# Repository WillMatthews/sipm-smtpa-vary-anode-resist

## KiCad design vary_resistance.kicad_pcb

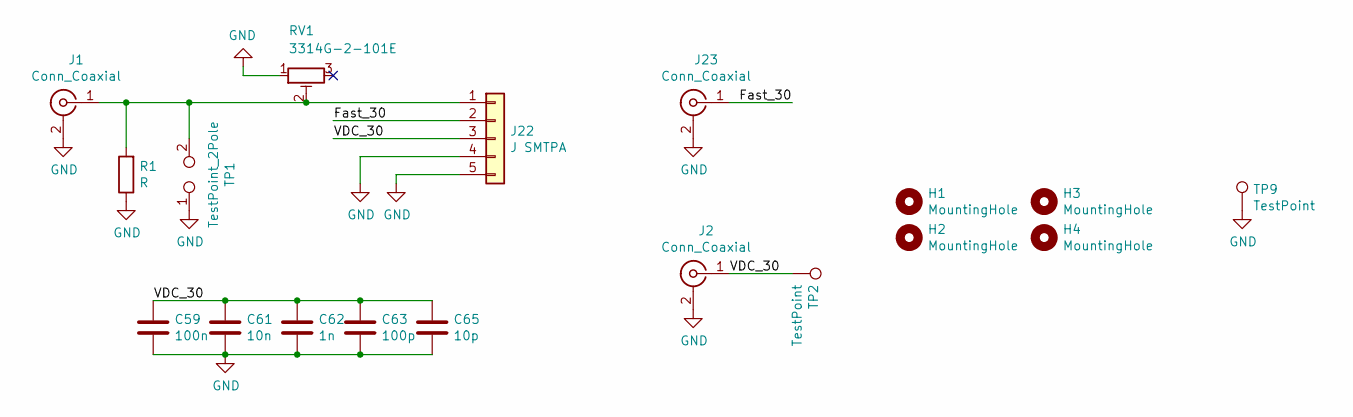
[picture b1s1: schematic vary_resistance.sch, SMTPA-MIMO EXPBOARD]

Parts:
C59: 100n; C_0603_1608Metric_Pad1.05x0.95mm_HandSolder
C61: 10n; C_0603_1608Metric_Pad1.05x0.95mm_HandSolder
C62: 1n; C_0603_1608Metric_Pad1.05x0.95mm_HandSolder
C63: 100p; C_0402_1005Metric
C65: 10p; C_0402_1005Metric
H1, H2, H3, H4: MountingHole; MountingHole_4.3mm_M4_Pad_Via
J1, J2, J23: Conn_Coaxial; SMA_Amphenol_132289_EdgeMount
J22: J SMTPA; SMTPA J30035
R1: R; R_0805_2012Metric_Pad1.15x1.40mm_HandSolder
RV1: 3314G-2-101E; Potentiometer_Bourns_3314G_Vertical; Part 987-1161-ND
TP1: TestPoint_2Pole; PinHeader_1x02_P2.54mm_Vertical
TP2, TP9: TestPoint; TestPoint_Pad_4.0x4.0mm

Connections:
/Fast_30: J22.2, J23.1 (In)
/VDC_30: C59.1, C61.1, C62.1, C63.1, C65.1, J2.1 (In), J22.3, TP2.1
GND: C59.2, C61.2, C62.2, C63.2, C65.2, J1.2 (Ext), J2.2 (Ext), J22.4, J22.5, J23.2 (Ext), R1.1, RV1.1, TP1.1, TP9.1
unnamed: J1.1 (In), J22.1, R1.2, RV1.2, TP1.2

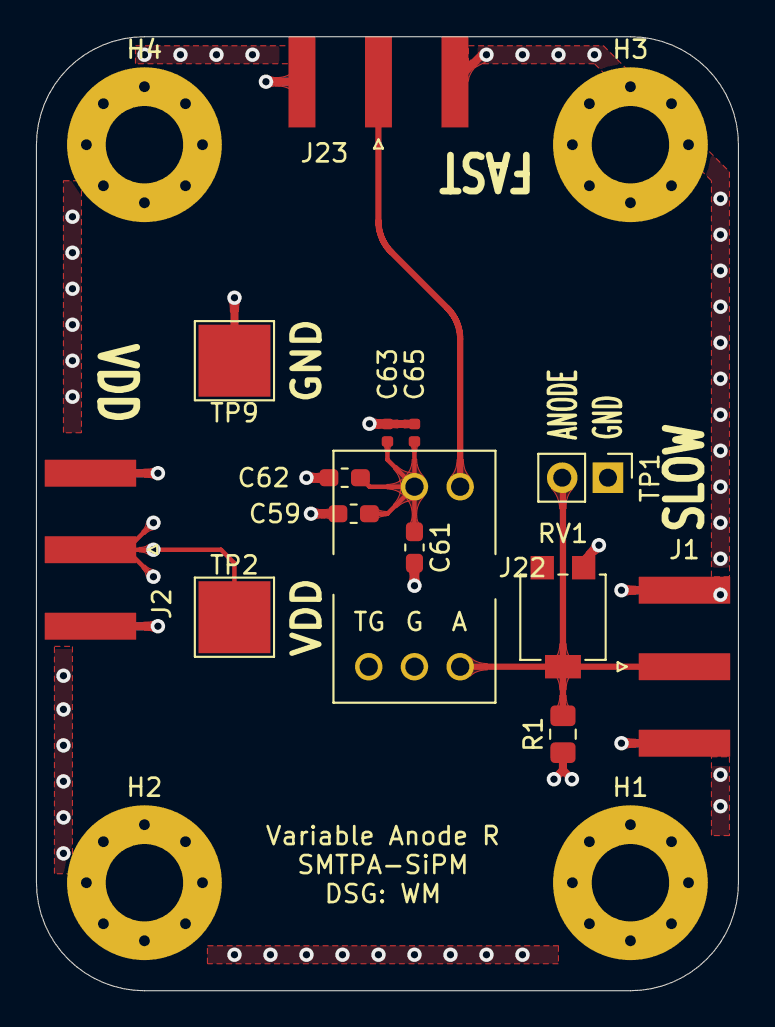
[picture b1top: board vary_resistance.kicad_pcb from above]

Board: 4 copper layers, 39.0 x 53.0 mm, 18 parts (0 on the bottom side), 4 nets.

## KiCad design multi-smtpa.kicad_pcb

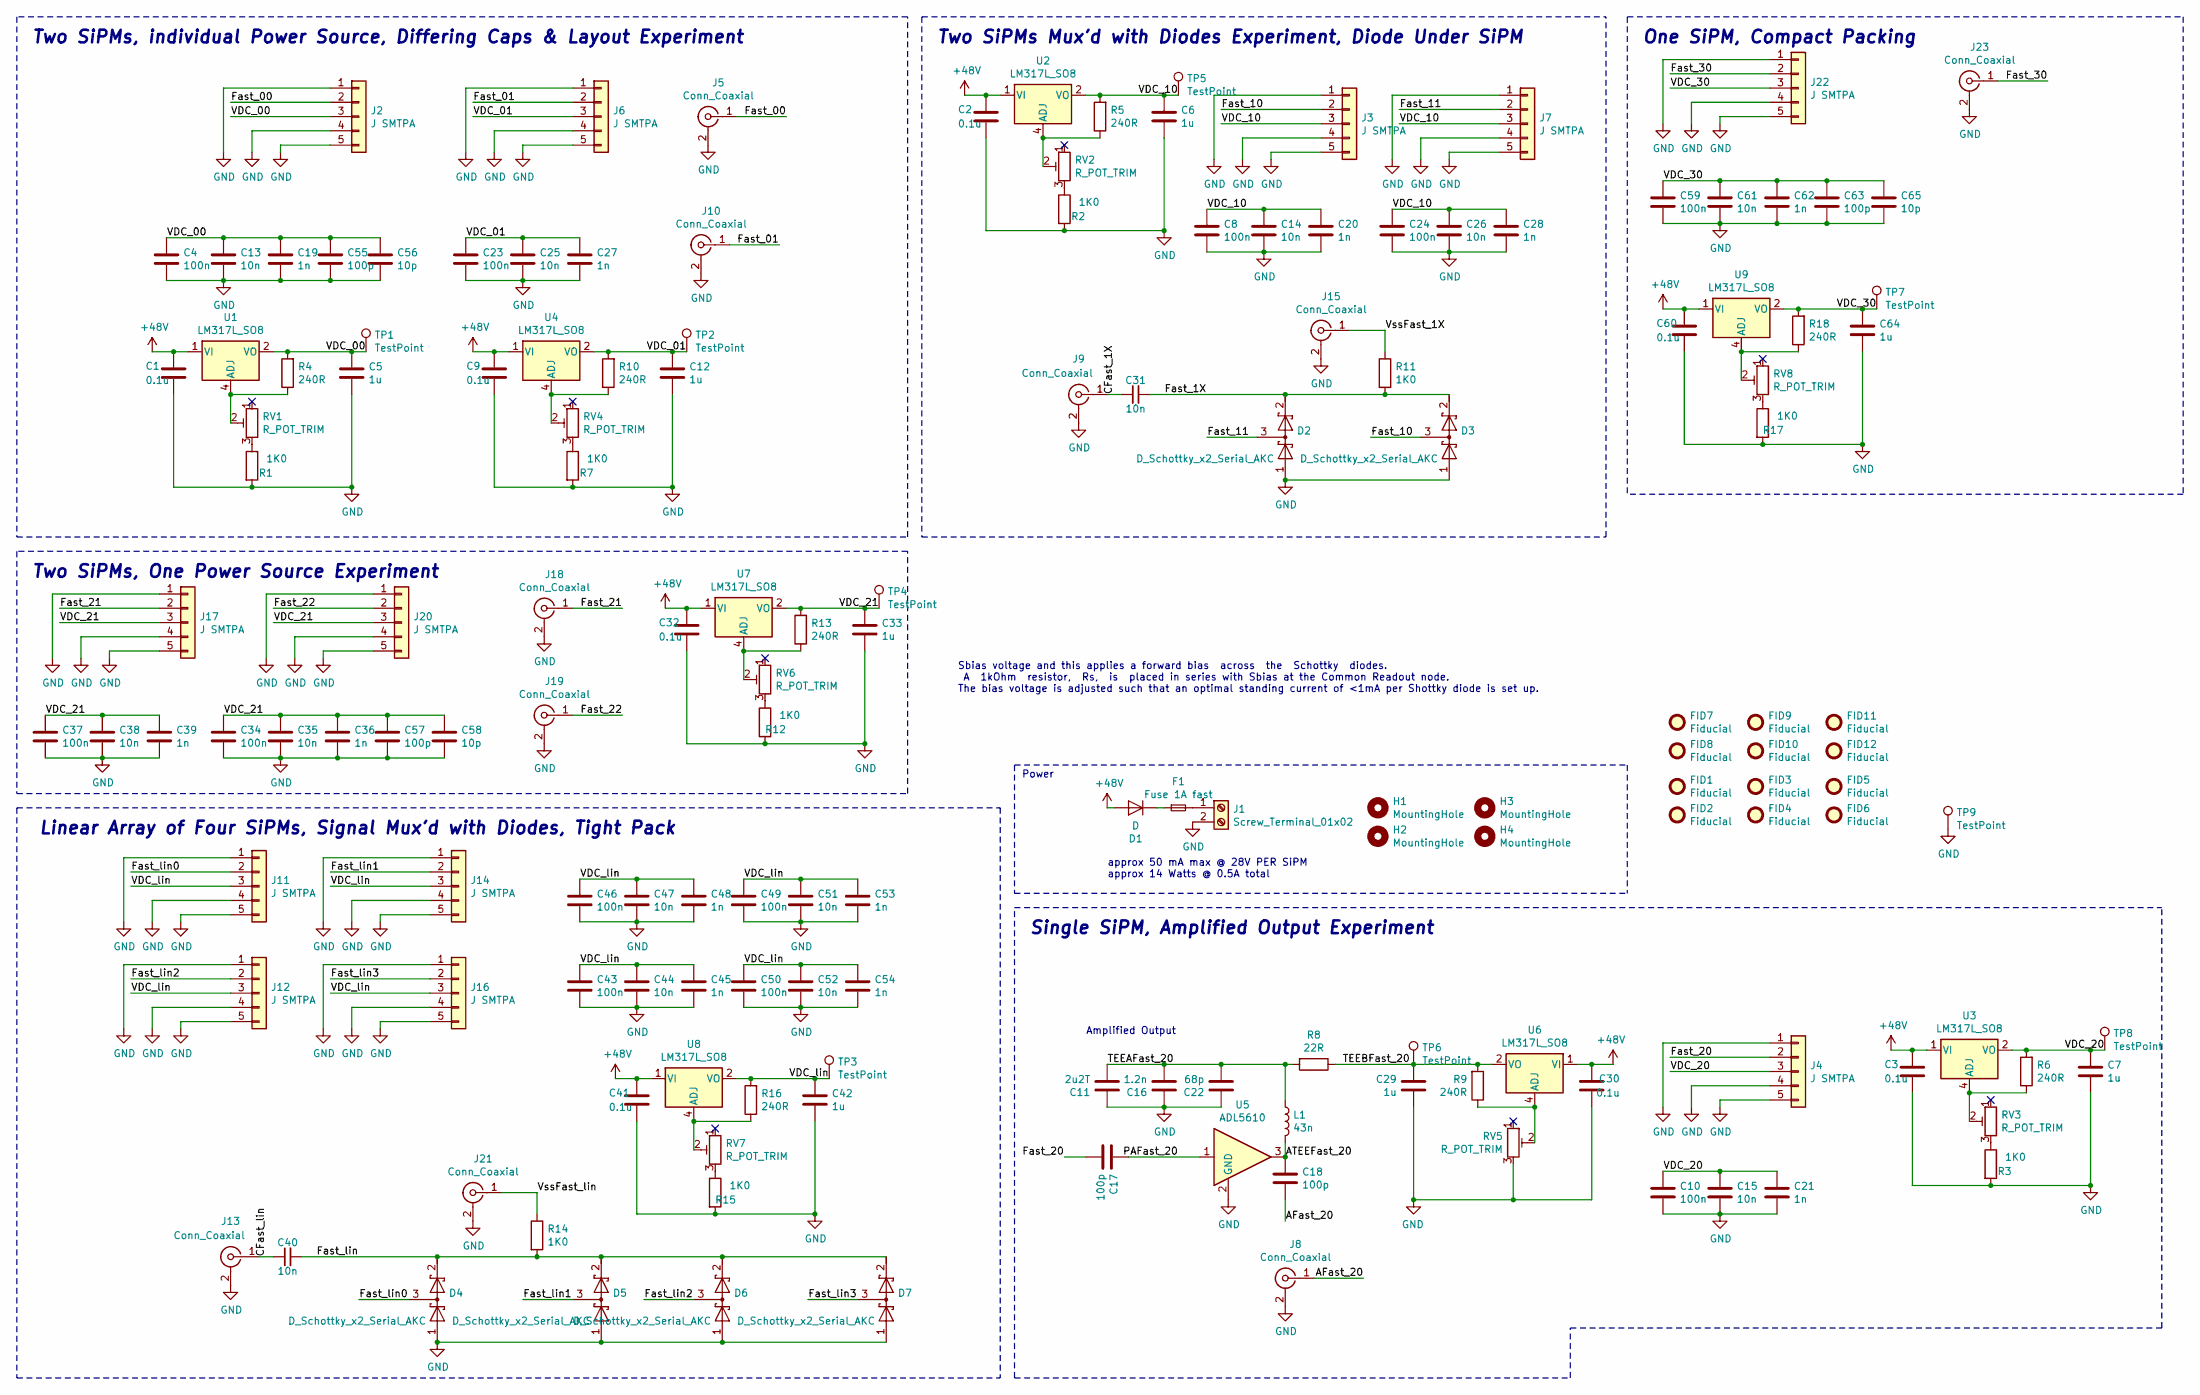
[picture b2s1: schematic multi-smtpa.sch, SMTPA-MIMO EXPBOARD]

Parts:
C1, C2, C3, C9, C30, C32, C41, C60: 0.1u; C_0805_2012Metric_Pad1.15x1.40mm_HandSolder
C4, C8, C10, C23, C24, C34, C37, C43, C46, C49, C50, C59: 100n; C_0603_1608Metric_Pad1.05x0.95mm_HandSolder
C5, C6, C7, C12, C29, C33, C42, C64: 1u; C_0805_2012Metric_Pad1.15x1.40mm_HandSolder
C11: 2u2T; C_0805_2012Metric_Pad1.15x1.40mm_HandSolder
C13, C14, C15, C25, C26, C31, C35, C38, C40, C44, C47, C51, C52, C61: 10n; C_0603_1608Metric_Pad1.05x0.95mm_HandSolder
C16: 1.2n; C_0603_1608Metric_Pad1.05x0.95mm_HandSolder
C17, C18: 100p; C_0603_1608Metric_Pad1.05x0.95mm_HandSolder
C19, C20, C21, C27, C28, C36, C39, C45, C48, C53, C54, C62: 1n; C_0603_1608Metric_Pad1.05x0.95mm_HandSolder
C22: 68p; C_0603_1608Metric_Pad1.05x0.95mm_HandSolder
C55, C57, C63: 100p; C_0402_1005Metric
C56, C58, C65: 10p; C_0402_1005Metric
D1: D; D_A-405_P10.16mm_Horizontal
D2, D3, D4, D5, D6, D7: D_Schottky_x2_Serial_AKC; SOT-23; Part SMS7621-005LF SOT23
F1: Fuse 1A fast; R_Axial_DIN0207_L6.3mm_D2.5mm_P10.16mm_Horizontal
FID1, FID2, FID3, FID4, FID5, FID6, FID7, FID8, FID9, FID10, FID11, FID12: Fiducial; Fiducial_1mm_Mask3mm
H1, H2, H3, H4: MountingHole; MountingHole_4.3mm_M4_Pad_Via
J1: Screw_Terminal_01x02; TerminalBlock_TE_282834-2_1x02_P2.54mm_Horizontal
J2, J3, J4, J6, J7, J11, J12, J14, J16, J17, J20, J22: J SMTPA; SMTPA J30035
J5, J8, J9, J10, J13, J15, J18, J19, J21, J23: Conn_Coaxial; SMA_Amphenol_132289_EdgeMount
L1: 43n; L_0402_1005Metric; part LQW15AN43NG00D
R1, R2, R3, R7, R12, R15, R17: 1K0; R_0805_2012Metric_Pad1.15x1.40mm_HandSolder
R4, R5, R6, R9, R10, R13, R16, R18: 240R; R_0805_2012Metric_Pad1.15x1.40mm_HandSolder
R8: 22R; R_0603_1608Metric_Pad1.05x0.95mm_HandSolder
R11, R14: 1K0; R_0603_1608Metric_Pad1.05x0.95mm_HandSolder
RV1, RV2, RV3, RV4, RV5, RV6, RV7: R_POT_TRIM; Potentiometer_Bourns_3006Y_Horizontal; Part 987-1161-ND
RV8: R_POT_TRIM; Potentiometer_Bourns_3314G_Vertical; Part 987-1161-ND
TP1, TP2, TP3, TP4, TP5, TP6, TP7, TP8: TestPoint; TestPoint_Pad_D2.0mm
TP9: TestPoint; TestPoint_Pad_4.0x4.0mm
U1, U2, U3, U4, U6, U7, U8, U9: LM317L_SO8; SOIC-8_3.9x4.9mm_P1.27mm; Part LM317LDR2GOSDKR-ND
U5: ADL5610; SOT-89-3

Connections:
+48V: C1.1, C2.1, C3.1, C9.1, C30.1, C32.1, C41.1, C60.1, D1.2 (A), U1.1 (VI), U2.1 (VI), U3.1 (VI), U4.1 (VI), U6.1 (VI), U7.1 (VI), U8.1 (VI), U9.1 (VI)
/AFast_20: C18.2, J8.1 (In)
/ATEEFast_20: C18.1, L1.2, U5.3
/CFast_1X: C31.1, J9.1 (In)
/CFast_lin: C40.1, J13.1 (In)
/Fast_00: J2.2, J5.1 (In)
/Fast_01: J6.2, J10.1 (In)
/Fast_1X: C31.2, D2.2 (K), D3.2 (K), R11.2
/Fast_10: D3.3 (common), J3.2
/Fast_11: D2.3 (common), J7.2
/Fast_20: C17.2, J4.2
/Fast_21: J17.2, J18.1 (In)
/Fast_22: J19.1 (In), J20.2
/Fast_30: J22.2, J23.1 (In)
/Fast_lin: C40.2, D4.2 (K), D5.2 (K), D6.2 (K), D7.2 (K), R14.2
/Fast_lin0: D4.3 (common), J11.2
/Fast_lin1: D5.3 (common), J14.2
/Fast_lin2: D6.3 (common), J12.2
/Fast_lin3: D7.3 (common), J16.2
/PAFast_20: C17.1, U5.1
/TEEAFast_20: C11.2, C16.2, C22.2, L1.1, R8.2
/TEEBFast_20: C29.1, R8.1, R9.2, TP6.1, U6.2 (VO), U6.3 (VO), U6.6 (VO), U6.7 (VO)
/VDC_00: C4.1, C5.1, C13.1, C19.1, C55.1, C56.1, J2.3, R4.2, TP1.1, U1.2 (VO), U1.3 (VO), U1.6 (VO), U1.7 (VO)
/VDC_01: C12.1, C23.1, C25.1, C27.1, J6.3, R10.2, TP2.1, U4.2 (VO), U4.3 (VO), U4.6 (VO), U4.7 (VO)
/VDC_10: C6.1, C8.1, C14.1, C20.1, C24.1, C26.1, C28.1, J3.3, J7.3, R5.2, TP5.1, U2.2 (VO), U2.3 (VO), U2.6 (VO), U2.7 (VO)
/VDC_20: C7.1, C10.1, C15.1, C21.1, J4.3, R6.2, TP8.1, U3.2 (VO), U3.3 (VO), U3.6 (VO), U3.7 (VO)
/VDC_21: C33.1, C34.1, C35.1, C36.1, C37.1, C38.1, C39.1, C57.1, C58.1, J17.3, J20.3, R13.2, TP4.1, U7.2 (VO), U7.3 (VO), U7.6 (VO), U7.7 (VO)
/VDC_30: C59.1, C61.1, C62.1, C63.1, C64.1, C65.1, J22.3, R18.2, TP7.1, U9.2 (VO), U9.3 (VO), U9.6 (VO), U9.7 (VO)
/VDC_lin: C42.1, C43.1, C44.1, C45.1, C46.1, C47.1, C48.1, C49.1, C50.1, C51.1, C52.1, C53.1, C54.1, J11.3, J12.3, J14.3, J16.3, R16.2, TP3.1, U8.2 (VO), U8.3 (VO), U8.6 (VO), U8.7 (VO)
/VssFast_1X: J15.1 (In), R11.1
/VssFast_lin: J21.1 (In), R14.1
GND: C1.2, C2.2, C3.2, C4.2, C5.2, C6.2, C7.2, C8.2, C9.2, C10.2, C11.1, C12.2, C13.2, C14.2, C15.2, C16.1, C19.2, C20.2, C21.2, C22.1, C23.2, C24.2, C25.2, C26.2, C27.2, C28.2, C29.2, C30.2, C32.2, C33.2, C34.2, C35.2, C36.2, C37.2, C38.2, C39.2, C41.2, C42.2, C43.2, C44.2, C45.2, C46.2, C47.2, C48.2, C49.2, C50.2, C51.2, C52.2, C53.2, C54.2, C55.2, C56.2, C57.2, C58.2, C59.2, C60.2, C61.2, C62.2, C63.2, C64.2, C65.2, D2.1 (A), D3.1 (A), D4.1 (A), D5.1 (A), D6.1 (A), D7.1 (A), J1.2, J2.1, J2.4, J2.5, J3.1, J3.4, J3.5, J4.1, J4.4, J4.5, J5.2 (Ext), J6.1, J6.4, J6.5, J7.1, J7.4, J7.5, J8.2 (Ext), J9.2 (Ext), J10.2 (Ext), J11.1, J11.4, J11.5, J12.1, J12.4, J12.5, J13.2 (Ext), J14.1, J14.4, J14.5, J15.2 (Ext), J16.1, J16.4, J16.5, J17.1, J17.4, J17.5, J18.2 (Ext), J19.2 (Ext), J20.1, J20.4, J20.5, J21.2 (Ext), J22.1, J22.4, J22.5, J23.2 (Ext), R1.2, R2.2, R3.2, R7.2, R12.2, R15.2, R17.2, RV5.3, TP9.1, U5.2 (GND)
unnamed: D1.1 (K), F1.1
unnamed: F1.2, J1.1
unnamed: R1.1, RV1.3
unnamed: R2.1, RV2.3
unnamed: R3.1, RV3.3
unnamed: R4.1, RV1.2, U1.4 (ADJ)
unnamed: R5.1, RV2.2, U2.4 (ADJ)
unnamed: R6.1, RV3.2, U3.4 (ADJ)
unnamed: R7.1, RV4.3
unnamed: R9.1, RV5.2, U6.4 (ADJ)
unnamed: R10.1, RV4.2, U4.4 (ADJ)
unnamed: R12.1, RV6.3
unnamed: R13.1, RV6.2, U7.4 (ADJ)
unnamed: R15.1, RV7.3
unnamed: R16.1, RV7.2, U8.4 (ADJ)
unnamed: R17.1, RV8.3
unnamed: R18.1, RV8.2, U9.4 (ADJ)

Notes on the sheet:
approx 50 mA max @ 28V PER SiPM approx 14 Watts @ 0.5A total
Power
Sbias voltage and this applies a forward bias across the Schottky diodes. A 1kOhm resistor, Rs, is placed in series with Sbias at the Common Readout node. The bias voltage is adjusted such that an optimal standing current of <1mA per Shottky diode is set up.
Amplified Output
Single SiPM, Amplified Output Experiment
Two SiPMs, One Power Source Experiment
Two SiPMs, individual Power Source, Differing Caps & Layout Experiment
Linear Array of Four SiPMs, Signal Mux'd with Diodes, Tight Pack
Two SiPMs Mux'd with Diodes Experiment, Diode Under SiPM
One SiPM, Compact Packing

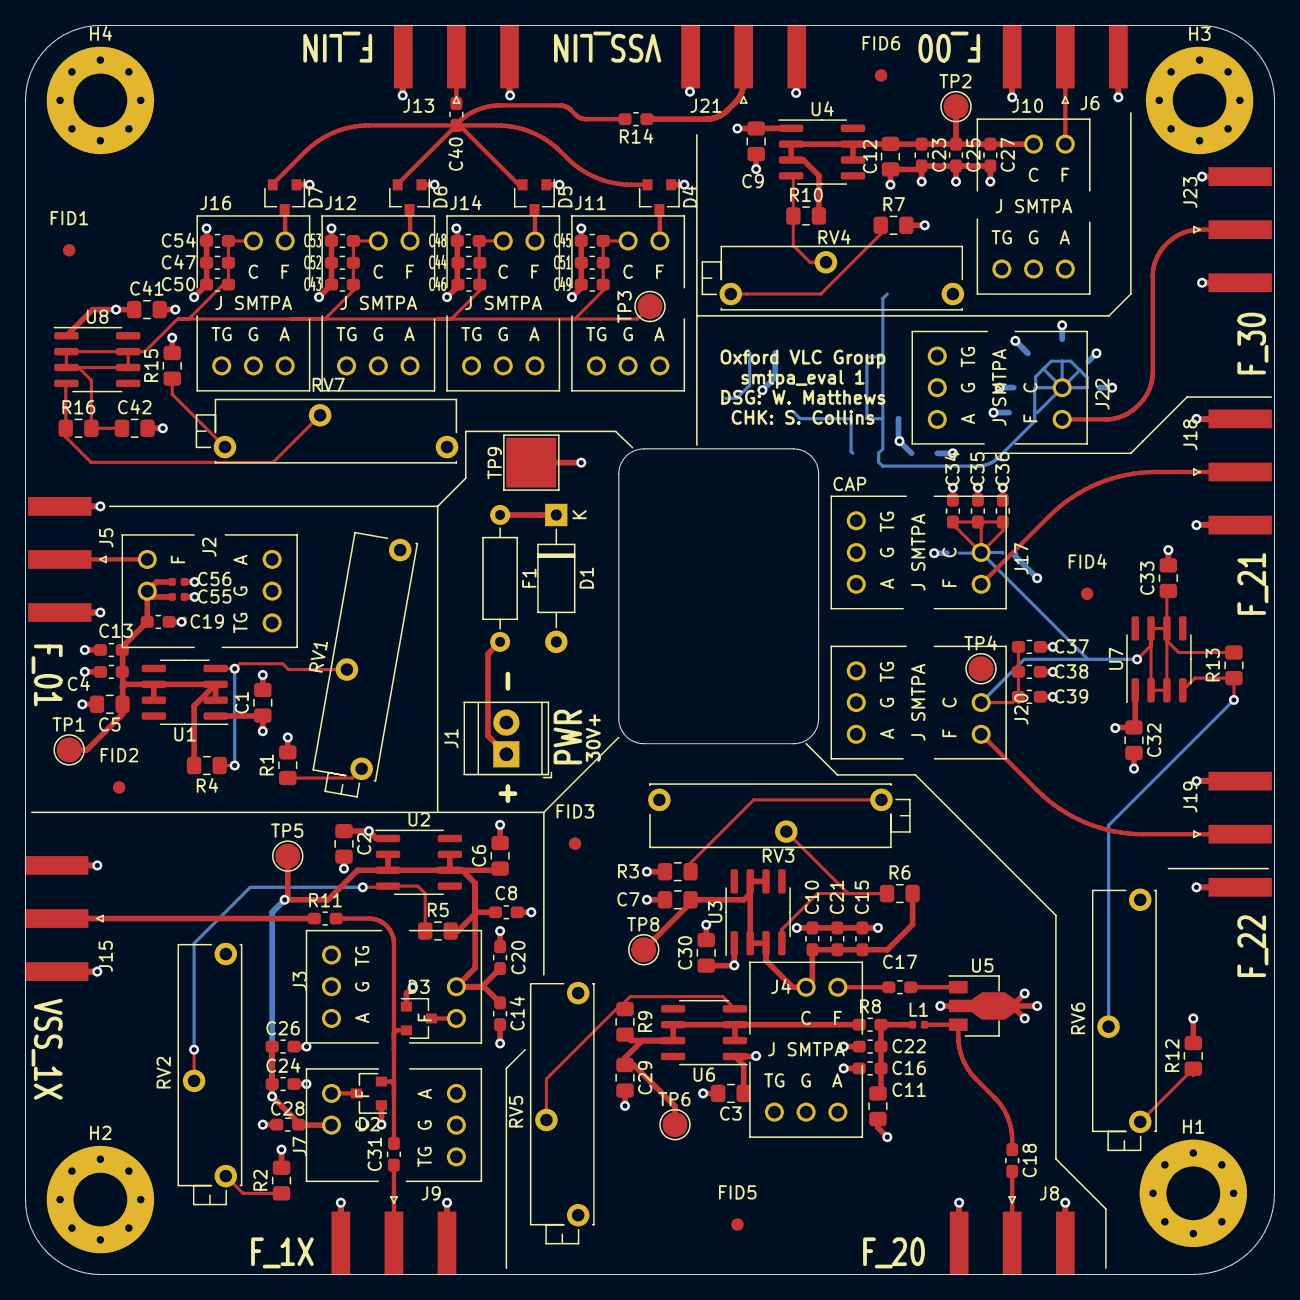
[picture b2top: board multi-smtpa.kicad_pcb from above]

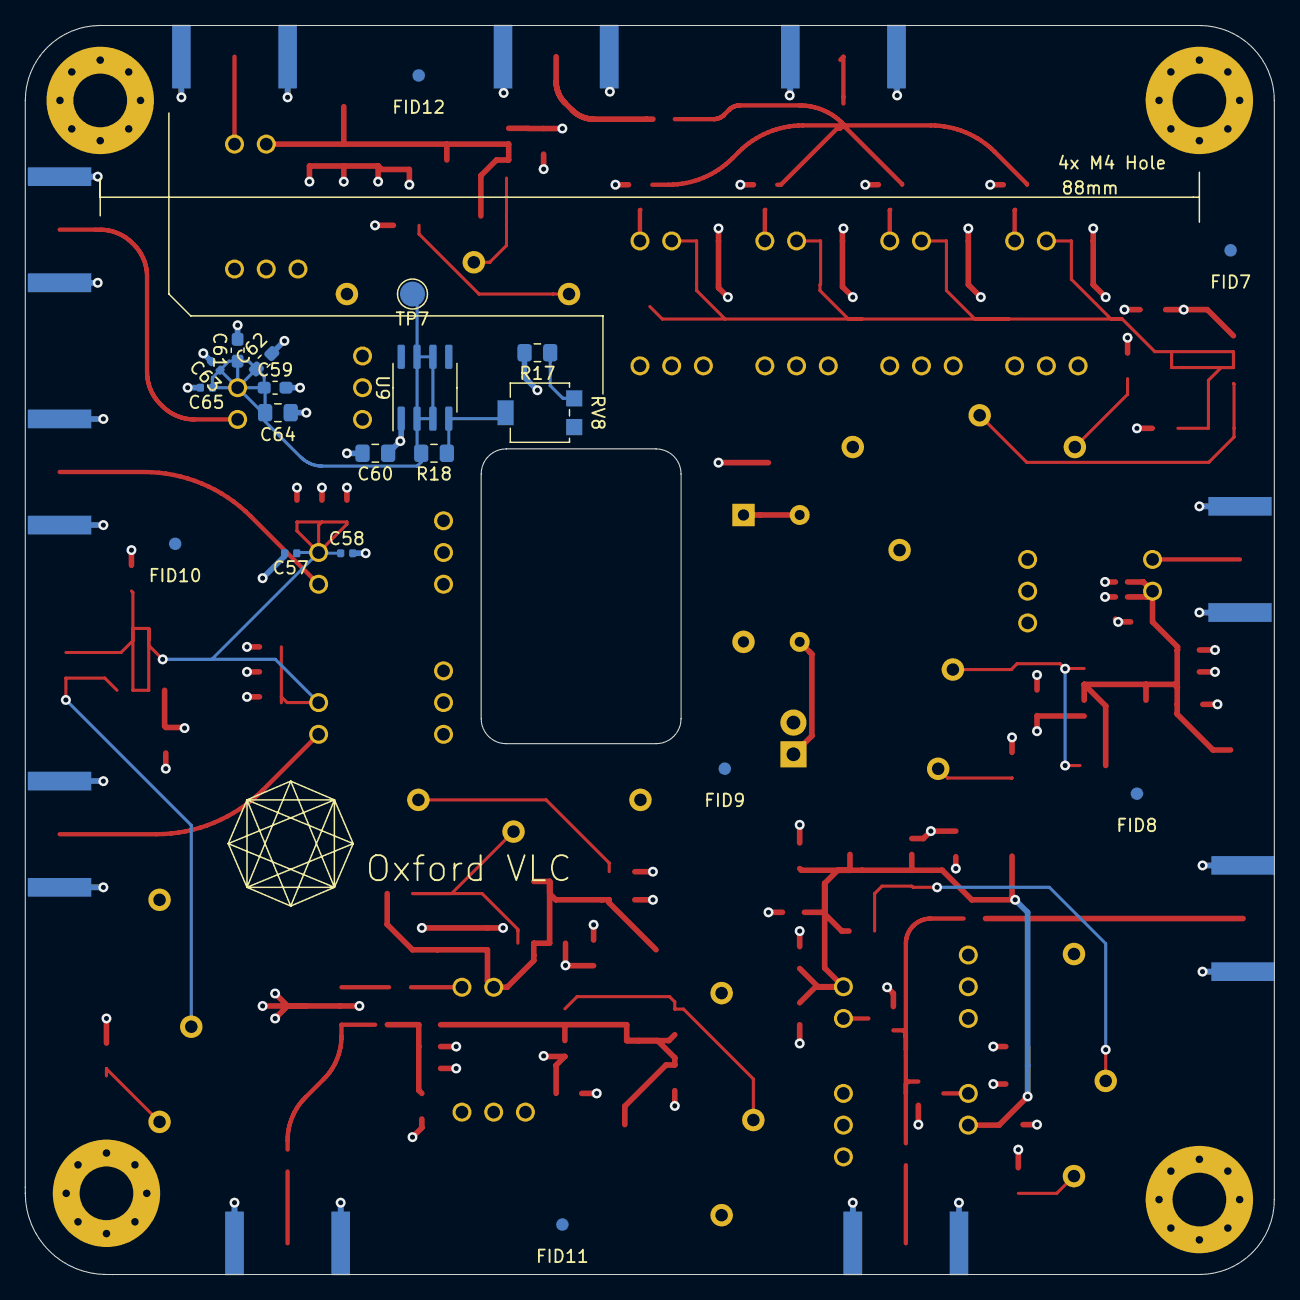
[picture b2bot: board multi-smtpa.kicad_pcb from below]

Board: 4 copper layers, 100.0 x 100.0 mm, 157 parts (20 on the bottom side), 49 nets.

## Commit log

2020-04-27 eval board done
2020-05-04 added another experiment, testpoints, fiducials
2024-04-06 vary-resistance single SiPM mount
2024-04-06 remove crap
